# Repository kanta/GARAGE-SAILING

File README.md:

# GARAGE SAILING
- [English](./README_en.md)
- [GARAGE SAILING FMラジオ](https://github.com/kanta/GARAGE-SAILING/tree/main/GarageSailing-FM-radio)

<Strong>梅田哲也 / ジョン・リチャーズ (Dirty Electronics) / ティム・ショウ / 堀尾寛太 </strong>

今冬、サウンド・アーティストのジョン・リチャーズ、ティム・ショウが来日します。2人はそれぞれ楽器や道具をDIYで製作し、UKを拠点に国際的に活躍しています。

Do a Front はもともと二人と交流がある日本のアーティスト・梅田哲也（大阪）と堀尾寛太（東京）を同時に招聘し、4人の滞在制作の成果公演として、日没のマジックアワーにガレージセールとセーリング（航海）をモチーフにした展覧会を開催します。

場内ではアーティストたちがそれぞれの作品テーマに基づいたショップを一時的にオープンし、観客はFMラジオをつかって、アーティストたちが発信する音を受信しながら会場内を移動していきます。ショップで制作した作品はその場で購入することもできます。

国際的に活躍する4人のワールドプレミアとなる新作公演にご期待ください！

## 日時
2022年12月10日（土）<br />
15:00 開場<br />
16:00 展覧会スタート、日没まで

2022年12月11日（日）<br />
10:00 ワークショップ＆製作物展示、日没まで

## 会場
[Do a front](https://www.doafront.org/about/index.html)<br />
山口県山口市堂の前町1-9

入場無料<br />
暖かいお飲み物の販売あり

- ヘッドホンおよび、イヤホンで聞けるFMラジオをご持参ください。
- お持ちでない方には会場で貸し出ししますが、数に限りがございます（滞在制作した自作ラジオを購入することもできます）。
- 会場は寒いので暖かくしてお越しください。

主催　Do a front

## 出演者
### 梅田哲也

建物の構造や周囲の環境から着想を得て、その場でしか成立しえない現象としての時間を演出する。これまで美術館や博物館での展覧会のほかに、劇場のパフォーマンス公演や、普段行き慣れない場所へ観客を招待するツアー型の作品を発表。近年の個展・公演には「梅田哲也 イン 別府『Ｏ滞』」（別府、2020-2021年）、「うたの起源」（福岡市美術館、福岡、2019-2020年）、「プレイタイム」（シアターコクーン、2020年）などがある。<br />
https://siranami.com/

### ジョン・リチャーズ (Dirty Electronics)

ジョン・リチャーズは90年代から音楽や舞台芸術の分野で活動するアーティスト。過去数回にわたって来日し、勅使河原三郎やメルツバウら他のアーティストたちとのコラボレーションを行ってきた。近年は大人数による電子音楽とDIY電子工作のパフォーマンスに関心を持ち、批評的な制作に焦点をあてた「ダーティー・エレクトロニクス」という概念を探求し、ワークショップ・インスタレーションやパフォーマンス・インスタレーション、執筆活動など、さまざまな方法で即興的な実線を行っている。<br />
https://www.dirtyelectronics.org/

### ティム・ショウ

音、光、コミュニケーション・メディアを扱うアーティスト。パフォーマンス、インスタレーション、サウンドウォークなどの形で作品を発表している。フィールドレコーディング、電子工作、ビデオ、モジュラーシンセシス、サウンドオブジェクト、自作ハードウェア、DIYソフトウェアなどを用いた彼の作品、録音、文章は「The Guardian」や「BBC」を中心とした数多くの国際的なメディアで紹介されている。初来日。<br />
https://tim-shaw.net/

### 堀尾寛太

日用品や自作の装置を使って音や光、磁力、位置などのエネルギーと物理的な動きを結びつけ、その場で自律的に発生する現象を作るライブパフォーマンスやインスタレーション作品を発表している。また、エンジニアとして触覚と振動に基づく電子楽器やインタフェースの開発・製作を行っている。近年の活動・展覧会には、ボアダムズの∈Y∋を中心としたユニット「FINALBY( )」（2021年〜）や、「streaming heritage 2021 autumn」（名古屋市内、2021年）などがある。<br />
https://horiokanta.com/

## クレジット
- 藏田章子：企画
- 尾中俊介 (Calamari inc)：フライヤーデザイン
- アリ・シャリフッディン：ハーブ・薬草茶
- 時里充：映像技術、映像機材協力
- 大脇理智：音響機材・映像機材協力
- 東岳志：音響ケーブル協力

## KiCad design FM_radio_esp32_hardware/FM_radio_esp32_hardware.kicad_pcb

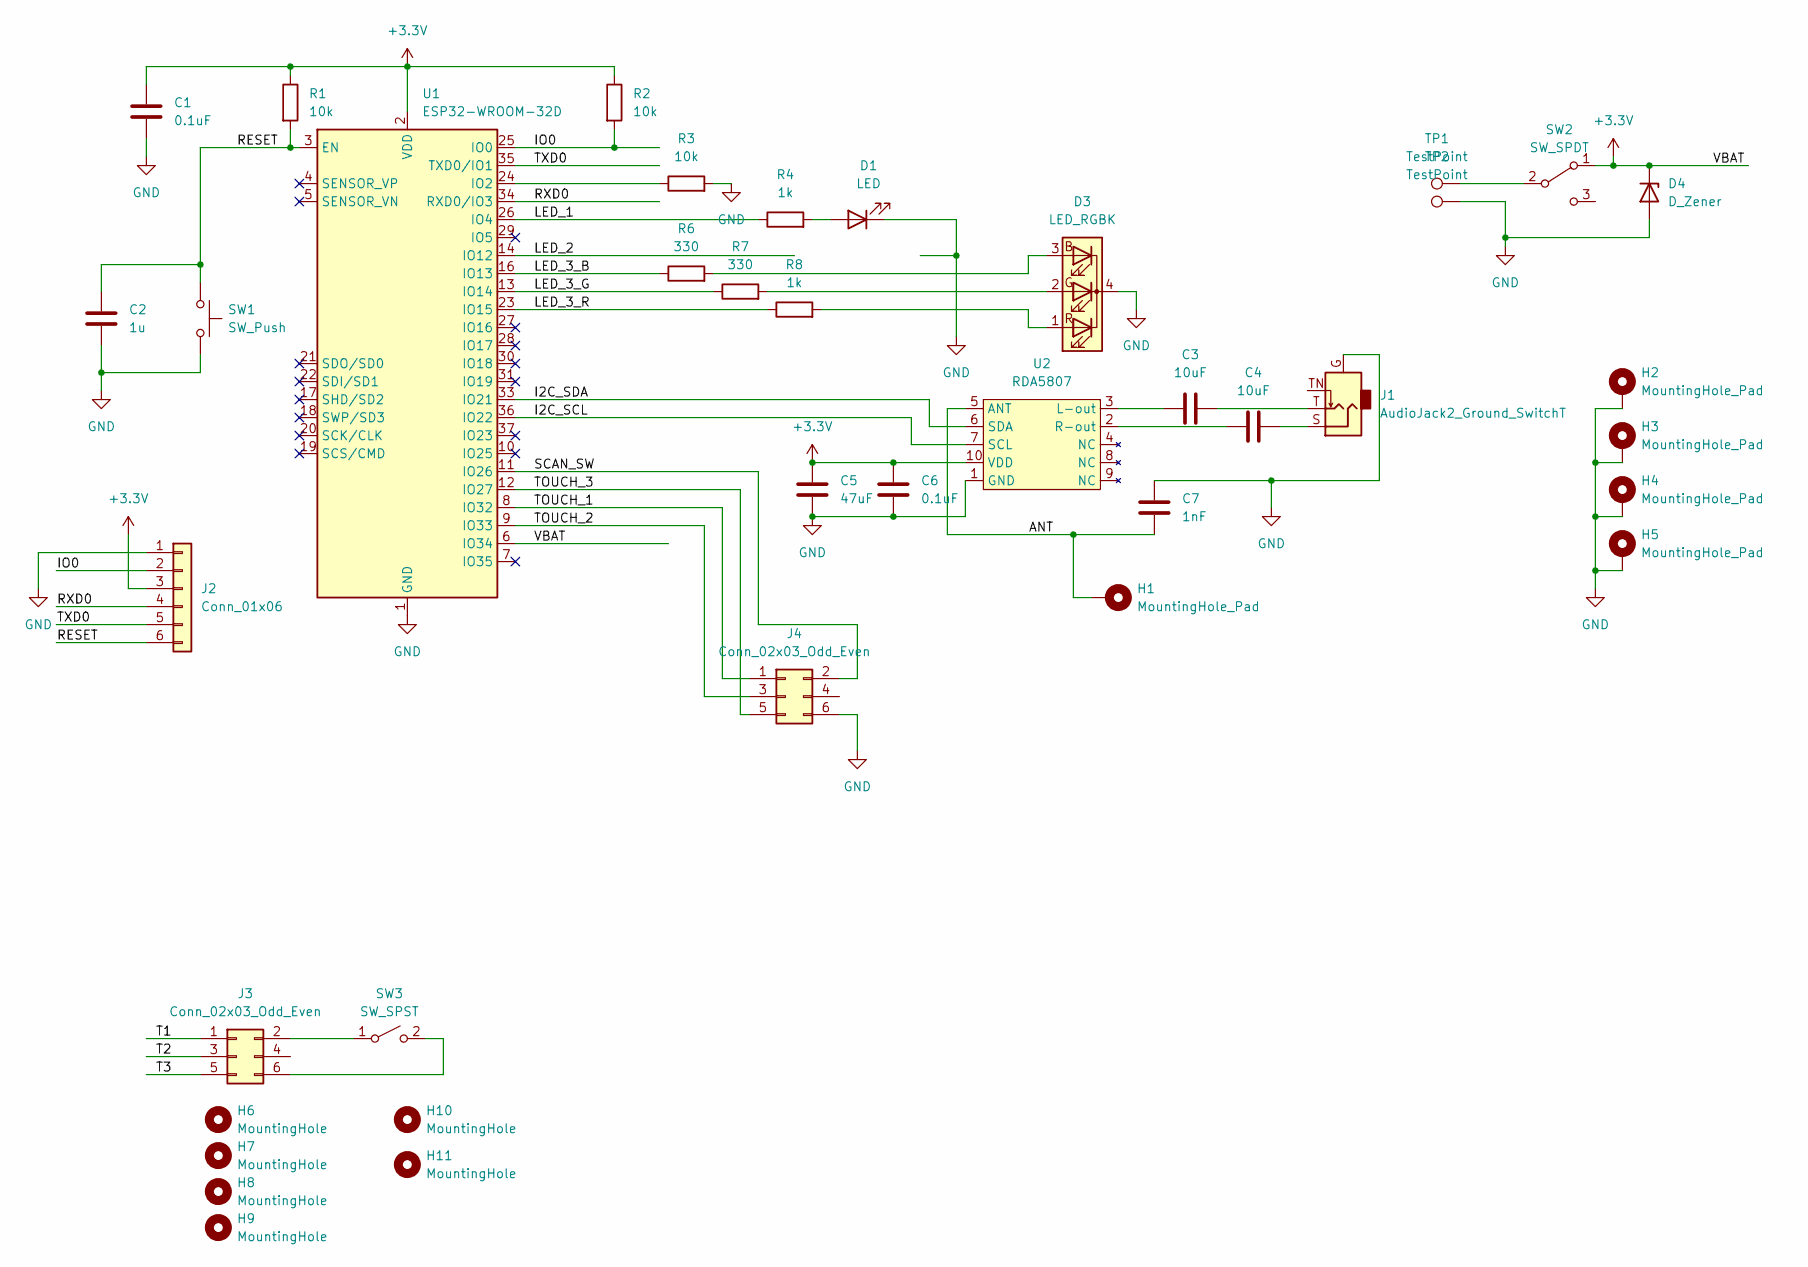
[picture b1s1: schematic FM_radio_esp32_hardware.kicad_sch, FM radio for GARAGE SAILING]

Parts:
C1, C6: 0.1uF; C_0603_1608Metric
C2: 1u; C_0603_1608Metric
C3, C4: 10uF; C_0805_2012Metric
C5: 47uF; C_1210_3225Metric
C7: 1nF; C_0603_1608Metric
D1: LED; LED_D3.0mm
D3: LED_RGBK; LED_D5.0mm-4_RGB_Wide_Pins
D4: D_Zener; D_SOD-323
H1: MountingHole_Pad; TestPoint_Keystone_5019_Minature
H2, H3, H4, H5: MountingHole_Pad; MountingHole_3.2mm_M3_Pad
H6, H7, H8, H9: MountingHole; MountingHole_3.2mm_M3
H10: MountingHole; Hole_8mm
H11: MountingHole; MountingHole_6.5mm
J1: AudioJack2_Ground_SwitchT; Jack_3.5mm_RS_913-1055
J2: Conn_01x06; PinHeader_1x06_P2.54mm_Vertical_SMD_Pin1Left
J3: Conn_02x03_Odd_Even; PinHeader_2x03_P2.54mm_Vertical_SMD
J4: Conn_02x03_Odd_Even; PinSocket_2x03_P2.54mm_Vertical_SMD
R1, R2, R3: 10k; R_0603_1608Metric
R4, R8: 1k; R_0603_1608Metric
R6, R7: 330; R_0603_1608Metric
SW1: SW_Push; SW_SPST_SKQG_WithoutStem
SW2: SW_SPDT; Toggle_Sw_1MS1-T1-B1-M1-Q-N
SW3: SW_SPST; SW_PUSH-12mm
TP1, TP2: TestPoint; TestPoint_Keystone_5019_Minature
U1: ESP32-WROOM-32D; ESP32-WROOM-32
U2: RDA5807; RDA5807H

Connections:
+3V3: C1.2, C5.1, C6.1, D4.1 (K), J2.3, R1.1, R2.1, SW2.1 (A), U1.2 (VDD), U1.6 (IO34), U2.10 (VDD)
/ANT: C7.2, H1.1, U2.5 (ANT)
/I2C_SCL: U1.36 (IO22), U2.7 (SCL)
/I2C_SDA: U1.33 (IO21), U2.6 (SDA)
/IO0: J2.2, R2.2, U1.25 (IO0)
/LED_1: R4.1, U1.26 (IO4)
/LED_2: U1.14 (IO12)
/LED_3_B: R6.1, U1.16 (IO13)
/LED_3_G: R7.1, U1.13 (IO14)
/LED_3_R: R8.1, U1.23 (IO15)
/RESET: C2.1, J2.6, R1.2, SW1.1, U1.3 (EN)
/RXD0: J2.4, U1.34 (RXD0/IO3)
/SCAN_SW: J4.2, U1.11 (IO26)
/T1: J3.1
/T2: J3.3
/T3: J3.5
/TOUCH_1: J4.1, U1.8 (IO32)
/TOUCH_2: J4.3, U1.9 (IO33)
/TOUCH_3: J4.5, U1.12 (IO27)
/TXD0: J2.5, U1.35 (TXD0/IO1)
GND: C1.1, C2.2, C5.2, C6.2, C7.1, D1.1 (K), D3.4 (K), D4.2 (A), H2.1, H3.1, H4.1, H5.1, J1.G, J2.1, J4.6, R3.2, SW1.2, TP2.1, U1.1 (GND), U1.15 (GND), U1.38 (GND), U1.39 (GND), U2.1 (GND)
unnamed: C3.1, U2.3 (L-out)
unnamed: C3.2, J1.T
unnamed: C4.1, U2.2 (R-out)
unnamed: C4.2, J1.S
unnamed: D1.2 (A), R4.2
unnamed: D3.1 (RA), R8.2
unnamed: D3.2 (GA), R7.2
unnamed: D3.3 (BA), R6.2
unnamed: J3.2, SW3.1 (A)
unnamed: J3.6, SW3.2 (B)
unnamed: R3.1, U1.24 (IO2)
unnamed: SW2.2 (B), TP1.1

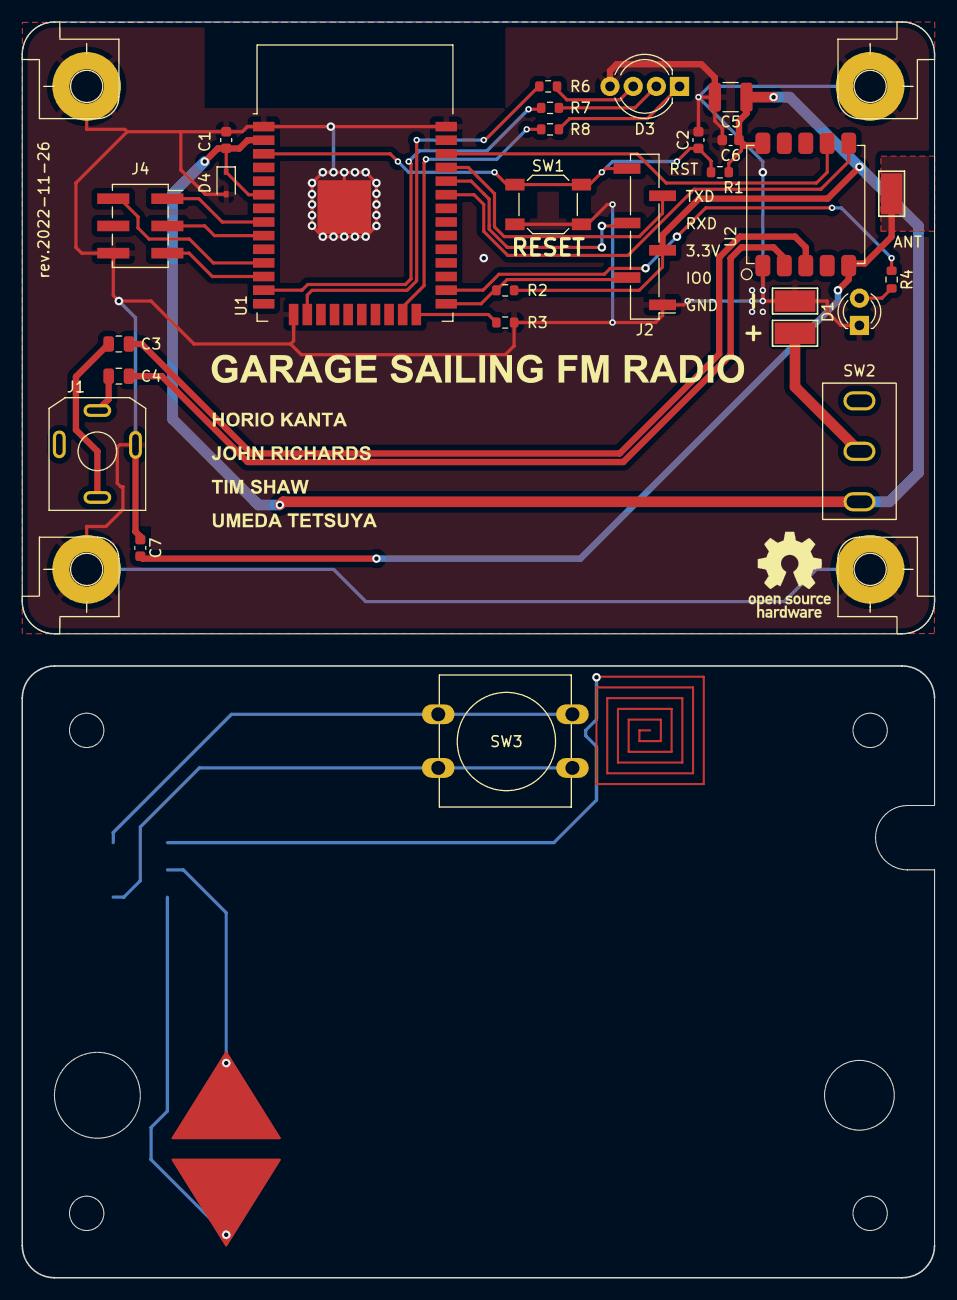
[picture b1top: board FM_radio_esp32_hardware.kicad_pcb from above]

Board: 2 copper layers, 85.0 x 117.0 mm, 39 parts (1 on the bottom side), 29 nets.

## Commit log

2022-11-17 first firmware test worked
2022-11-20 Test pu2clr library
2022-11-21 a schematic update
2022-11-23 Schematic updates
2022-11-24 added, side panel project. dimensions are need to be fixed
2022-11-25 side panels dimension update
2022-11-25 minor improvements
2022-11-26 fix a too big silk pattern
2022-11-26 new panelized data for side panels,
2022-11-30 firmware simplified
2022-11-30 Organize directories
2022-11-30 Added radio drawings
2022-12-02 Changed resistors value for the RGB LED.
2022-12-04 LED soldering jigs, corner post for the housing
2022-12-04 RGB led pin arrangements hacks
2022-12-05 Silk screen for a the radio panel
2022-12-05 色味調整
2022-12-05 Update sodering jigs
2022-12-06 ghost radio, LED spectrum freq indicator etc
2022-12-06 Create a Max test project
2022-12-08 some silk screen data
2022-12-08 Max test project
2022-12-08 Silk screen data organized
2022-12-09 split audio - video
2022-12-10 After the performance snapshot
